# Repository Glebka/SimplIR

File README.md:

# SimplIR

The project of a joined IR Remote for controlling both Samsung LE26B450 TV and unknown TV Box that uses RC5 IR protocol.
SimplIR allows to switch TV On and Off, control volume and switch channels on TV Box.

## Hardware and Software

* ATmega48PA MCU with Arduino based firmware
* 5 tactile buttons
* 1 5mm IR LED
* CR-2030 battery
* Firmware uses [Arduino-IRremote](https://github.com/Arduino-IRremote/Arduino-IRremote) for sending codes to the TV Set and TV Box
* Low power consumption - 0.1 uA, when in sleep mode (most of the time)

## TODO

* increase IR LED power, probably, add more LEDs in parallel
* add external crystal to guarantee precise timings
* deal with low recognition rate of ON/OFF signal for Samsung TV

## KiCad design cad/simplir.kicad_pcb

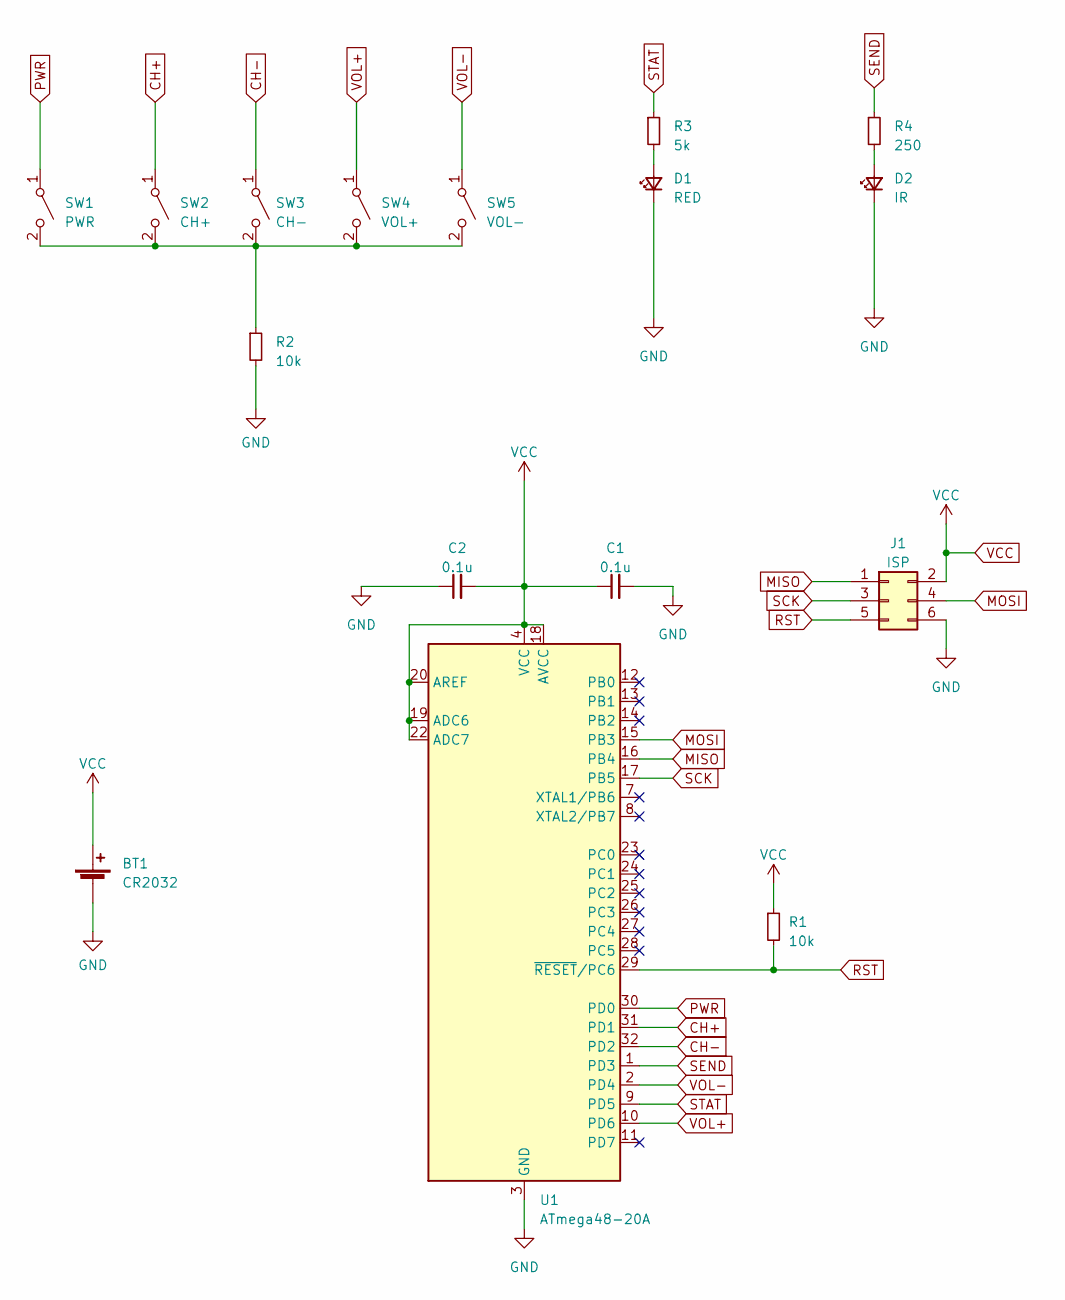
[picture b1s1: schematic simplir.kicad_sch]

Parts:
BT1: CR2032; BatteryHolder_Keystone_106_1x20mm
C1, C2: 0.1u; C_0805_2012Metric
D1: RED; LED_1206_3216Metric
D2: IR; LED_D5.0mm_IRGrey
J1: ISP; PinHeader_2x03_P2.54mm_Vertical
R1, R2: 10k; R_0805_2012Metric
R3: 5k; R_0805_2012Metric
R4: 250; R_0805_2012Metric
SW1: PWR; SW_SPST_TL3342
SW2: CH+; SW_SPST_TL3342
SW3: CH-; SW_SPST_TL3342
SW4: VOL+; SW_SPST_TL3342
SW5: VOL-; SW_SPST_TL3342
U1: ATmega48-20A; TQFP-32_7x7mm_P0.8mm

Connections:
CH+: SW2.1 (A), U1.31 (PD1)
CH-: SW3.1 (A), U1.32 (PD2)
GND: BT1.2 (-), C1.2, C2.1, D1.1 (K), D2.1 (K), J1.6, R2.2, U1.3 (GND), U1.5 (GND), U1.21 (GND)
MISO: J1.1, U1.16 (PB4)
MOSI: J1.4, U1.15 (PB3)
unnamed: D1.2 (A), R3.2
unnamed: D2.2 (A), R4.2
unnamed: R2.1, SW1.2 (B), SW2.2 (B), SW3.2 (B), SW4.2 (B), SW5.2 (B)
PWR: SW1.1 (A), U1.30 (PD0)
RST: J1.5, R1.2, U1.29 (~RESET/PC6)
SCK: J1.3, U1.17 (PB5)
SEND: R4.1, U1.1 (PD3)
STAT: R3.1, U1.9 (PD5)
VCC: BT1.1 (+), C1.1, C2.2, J1.2, R1.1, U1.4 (VCC), U1.6 (VCC), U1.18 (AVCC), U1.19 (ADC6), U1.20 (AREF), U1.22 (ADC7)
VOL+: SW4.1 (A), U1.10 (PD6)
VOL-: SW5.1 (A), U1.2 (PD4)

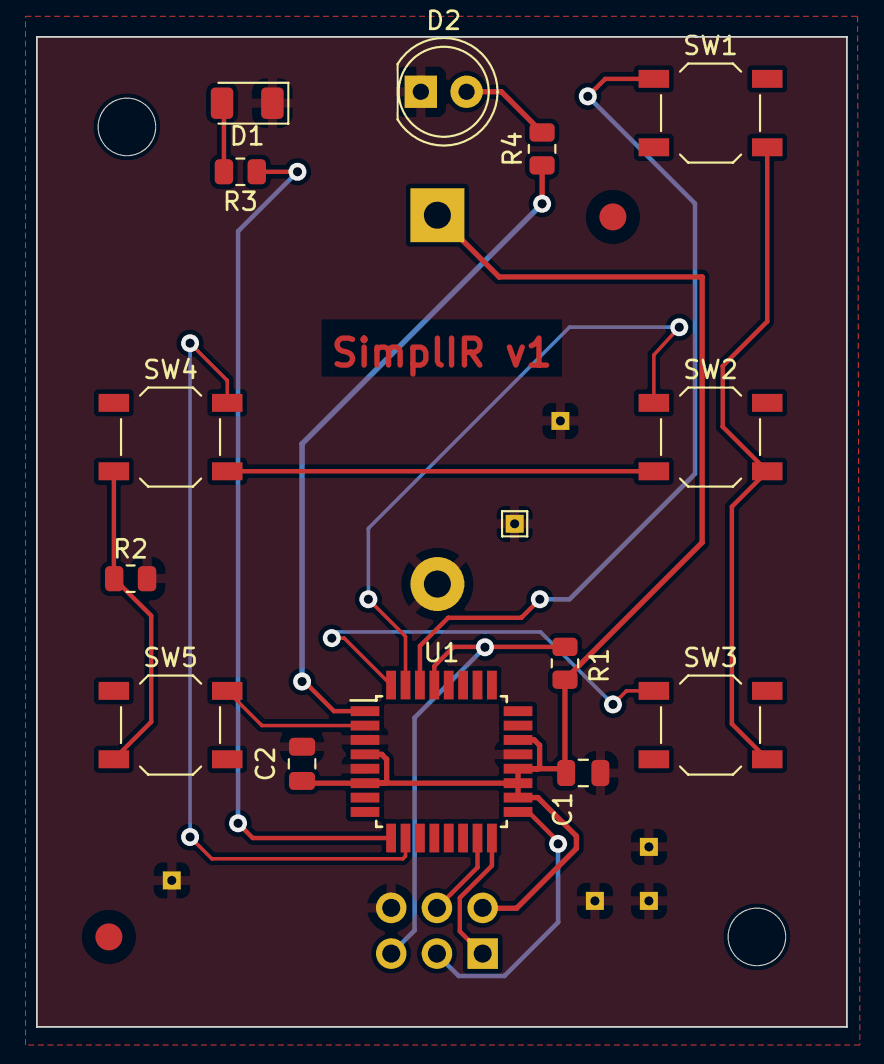
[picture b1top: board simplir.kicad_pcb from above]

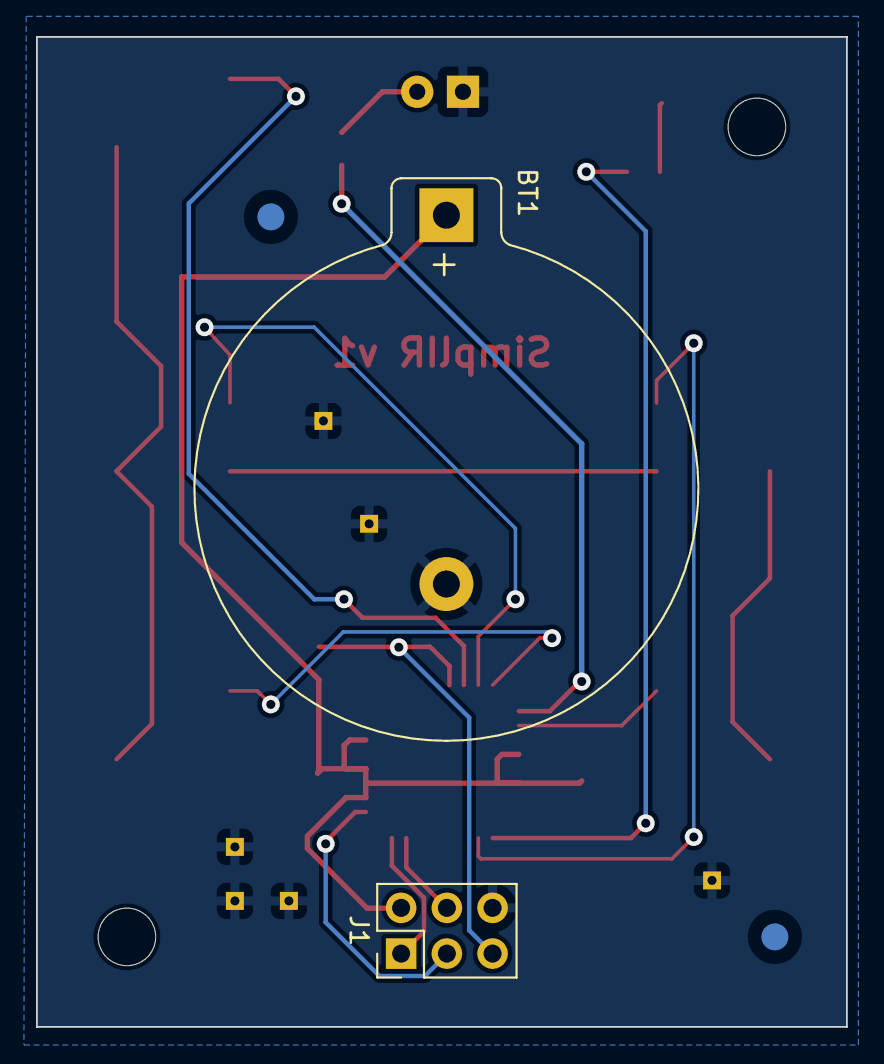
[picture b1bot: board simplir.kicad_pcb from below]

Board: 2 copper layers, 45.0 x 55.0 mm, 16 parts (2 on the bottom side), 16 nets.

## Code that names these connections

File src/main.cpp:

#include <Arduino.h>
#define DISABLE_CODE_FOR_RECEIVER
#define SEND_PWM_BY_TIMER
#define IR_USE_AVR_TIMER2
#include <IRremote.hpp>
#include <TimerOne.h>
#include <avr/power.h>
#include <avr/sleep.h>

#define IR_LED_PIN (PD3)
#define LED_FEEDBACK_PIN (PD5)
#define TICK_INTERVAL (30000)
#define IDLE_TICKS_TIMEOUT (5)

/*
PWR   - PD0
CH+   - PD1
CH-   - PD2
VOL-  - PD4
VOL+  - PD6
*/

namespace Buttons
{
  enum
  {
    BTN_PWR,
    CH_PLUS,
    CH_MINUS,
    VOL_MINUS,
    VOL_PLUS,
    COUNT_
  };
}

typedef void (*SendFunc)(uint16_t, uint16_t);

struct ButtonHandler
{
  SendFunc send;
  uint16_t addr;
  uint16_t cmd;
};

void send_rc5(uint16_t addr, uint16_t cmd)
{
  IrSender.sendRC5((uint8_t)addr, (uint8_t)cmd, 0);
}

void send_samsung(uint16_t addr, uint16_t cmd)
{
  IrSender.sendSamsung(addr, cmd, 0);
}

volatile uint8_t button_pins[Buttons::COUNT_] = {PD0, PD1, PD2, PD4, PD6};
volatile uint8_t buttons_prev_state[Buttons::COUNT_] = {1, 1, 1, 1, 1};
volatile uint8_t buttons_state[Buttons::COUNT_] = {1, 1, 1, 1, 1};
volatile uint8_t tick = 0;
volatile uint8_t ticks_since_last_event = 0;
ButtonHandler button_handlers[Buttons::COUNT_] = {
    {send_samsung, 0x707, 0x2},
    {send_rc5, 0xE, 0x3C},
    {send_rc5, 0xE, 0x11},
    {send_rc5, 0xE, 0x13},
    {send_rc5, 0xE, 0x12},
};

void inc_tick()
{
  tick++;
  ticks_since_last_event++;
}

void setup()
{
  // disable ADC
  ADCSRA = 0;

  // turn off various modules
  power_all_disable();

  // but enable the necessary ones
  power_timer0_enable();
  power_timer1_enable();
  power_timer2_enable();

  // set input with pull-up for all ports
  DDRB = 0;
  DDRC = 0;
  DDRD = 0;
  PORTB = 255;
  PORTC = 255;
  PORTD = 255;

  // IR Led pin should be OUTPUT
  pinMode(IR_LED_PIN, OUTPUT);
  digitalWrite(IR_LED_PIN, LOW);

  // Feedback pin is OUTPUT as well
  pinMode(LED_FEEDBACK_PIN, OUTPUT);
  digitalWrite(LED_FEEDBACK_PIN, LOW);

  // enable interrupts for PD
  PCICR |= 0b00000100;

  // enable interrupts for D0, D1, D2, D4, D6
  PCMSK2 |= 0b01010111;

  IrSender.begin(true, LED_FEEDBACK_PIN);
  Timer1.initialize(TICK_INTERVAL);
  Timer1.attachInterrupt(inc_tick);
}

void power_down()
{
  set_sleep_mode(SLEEP_MODE_PWR_DOWN);
  cli();
  sleep_enable();
  sleep_bod_disable();
  sei();
  sleep_cpu();
}

void idle()
{
  set_sleep_mode(SLEEP_MODE_IDLE);
  cli();
  sleep_enable();
  sleep_bod_disable();
  sei();
  sleep_cpu();
}

void read_pins()
{
  for (uint8_t i = 0; i < Buttons::COUNT_; i++)
  {
    buttons_state[i] = digitalRead(button_pins[i]);
  }
}

void update_previous_state()
{
  for (uint8_t i = 0; i < Buttons::COUNT_; i++)
  {
    buttons_prev_state[i] = buttons_state[i];
  }
}

uint8_t get_released_button()
{
  for (uint8_t i = 0; i < Buttons::COUNT_; i++)
  {
    if (buttons_prev_state[i] == 0 && buttons_state[i] == 1)
    {
      return i;
    }
  }
  return Buttons::COUNT_;
}

void loop()
{
  if (tick)
  {
    cli();
    tick = 0;
    read_pins();
    uint8_t button_pressed = get_released_button();
    update_previous_state();
    digitalWrite(LED_FEEDBACK_PIN, LOW);
    if (button_pressed != Buttons::COUNT_)
    {
      sei();
      Timer1.stop();
      ButtonHandler *handler_ptr = &button_handlers[button_pressed];
      handler_ptr->send(handler_ptr->addr, handler_ptr->cmd);
      ticks_since_last_event = 0;
      digitalWrite(LED_FEEDBACK_PIN, HIGH);
      Timer1.start();
    }
    sei();
    if (ticks_since_last_event >= IDLE_TICKS_TIMEOUT)
    {
      power_down();
    }
  }
  idle();
}

EMPTY_INTERRUPT(PCINT2_vect);

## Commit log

2023-05-07 Fix Volume+ and Volume- buttons
2023-05-07 Add CAD files and README
